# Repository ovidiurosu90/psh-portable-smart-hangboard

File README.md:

# [PSH Portable Smart Hangboard](https://github.com/ovidiurosu90/psh-portable-smart-hangboard)

## Abstract
### Problem
Help people get better at climbing by improving their finger strength

### Solution
Provide a portable smart hangboard to use for finger strength training

### How
- the whole project is open-source, and can be replicated by interested parties (note it requires a variety of skills like setting up a web server, 3d printing, soldering & crimping)
- the hangboard measures the pressure applied to the hanghold by using a couple of load cells
- the training plans are set in Google Sheets

## Important Links

| Name | README |
| --------------------- | ------------- |
| BOM Bill Of Materials | [BOM.md](BOM.md) |
| How To Build | [HOWTOBUILD.md](HOWTOBUILD.md) |

## Images

## Functionality of switches
- There are 3 big black momentary switches (labeled SW1, SW2 and SW3)
- There are 3 small toggle switches (labeled SW4, SW5 and SW6)
- The functionality of the switches is described below

### SW1
If SW4 is toggled ON: start training

Else: decrease volume

### SW2
If SW4 is toggled ON: start calibrating

Else: store volume into NVS (only if SW5 is toggled ON)

### SW3
If SW4 is toggled ON: end training

Else: increase volume

### SW4
If toggled ON: show train menu

Else: show volume menu

### SW5
If toggled ON: allow NVS to be updated (for calibration and for volume)

Else: don't allow NVS to be updated

### SW6
Not used at the moment

## Usage
- Power the microcontroller via its micro-USB port (+5V)
- Wait for the microcontroller to finish setting things up (it's ready when it says 'idle' on the lower left side of analog meter)
- Configure the training parameters in the spreadsheet via Goole Sheets
- The training program starts with a rest cycle, followed by an activity cycle, then repeat
- Example

| totalCycles | activityTotalSeconds | restTotalSeconds | scaleLowerLimitGrams | scaleUpperLimitGrams |
| ----------- | -------------------- | ---------------- | -------------------- | -------------------- |
| 6           | 10                   | 20               | 55000                | 90000                |

- For the example above, we'll have 6 cycles as follows:
    - cycle 1: rest for 20 seconds
    - cycle 2: activity for 10 seconds
    - cycle 3: rest for 20 seconds
    - cycle 4: activity for 10 seconds
    - cycle 5: rest for 20 seconds
    - cycle 6: activity for 10 seconds

- Start the training by pressing SW1 (note SW4 should be toggled ON)
- The score is updated only in the activity cycles (cycle 2, 4 and 6 in the example above)
- The score is calculated as follows:
    - each second there are 2 scale measurements
    - let's say we have 3 activity cycles of 10 seconds
    - which means 3x 10x 2 measurements
    - we just sum up the 60 measurements (in kg)
- For the exapmle above, the score can be the following:
    - score: 2017 (which is a sum of all the scale measurements)
    - history: 73,70,70,68,71,70,70,70,69,70,62,65,67,68,66,66,66,67,64,64,68,66,67,67,67,65,66,67,65,63
- In the future, the scoring method may be different, as at the moment, we don't penalize out-of-bounds measurements, and we don't reward in-bounds measurements

## Wiring

| [NodeMcu ESP-32S Lua ESP-WROOM-32](https://opencircuit.shop/product/nodemcu-esp-32s-lua-esp-wroom-32-wifi) | [SparkFun HX711 Load Cell Amplifier](https://eu.robotshop.com/products/hx711-load-cell-amplifier?variant=42600661942440) => NOTE we need to solder male pins |
| ---------------------------------------------------------------------------------------------------------- | ------------------------------------------------------------------------------------------------------------------------------------------------------------ |
| 5, 4                                                                                                       | DAT1, CLK1                                                                                                                                                   |
| 16, 15                                                                                                     | DAT2, CLK2                                                                                                                                                   |
| +3.3V                                                                                                      | VDD, VCC                                                                                                                                                     |
| GND                                                                                                        | GND                                                                                                                                                          |

| [NodeMcu ESP-32S Lua ESP-WROOM-32](https://opencircuit.shop/product/nodemcu-esp-32s-lua-esp-wroom-32-wifi) | [AZDelivery ST7735 SPI TFT Display 1.8 inch 128 x 160 pixels](https://www.amazon.nl/dp/B078J5TS2G/ref=pe_28126711_487805961_TE_item?th=1) =>  [guide](https://www.az-delivery.de/en/blogs/azdelivery-blog-fur-arduino-und-raspberry-pi/1-8-toll-tft-am-esp-32-dev-kit-c-betreiben) |
| ---------------------------------------------------------------------------------------------------------- | ---------------------------------------------------------------------------------------------------------------------------------------------------------------------------------------------------------------------------------------------------------------------------------- |
| +5V                                                                                                        | VCC                                                                                                                                                                                                                                                                                |
| GND                                                                                                        | GND                                                                                                                                                                                                                                                                                |
| G17                                                                                                        | CS                                                                                                                                                                                                                                                                                 |
| G14                                                                                                        | Reset / RST                                                                                                                                                                                                                                                                        |
| G2                                                                                                         | A0 / DC                                                                                                                                                                                                                                                                            |
| G23                                                                                                        | Sda / MOSI                                                                                                                                                                                                                                                                         |
| G18                                                                                                        | Sck / SCLK                                                                                                                                                                                                                                                                         |
| 3.3V                                                                                                       | LED                                                                                                                                                                                                                                                                                |

| [NodeMcu ESP-32S Lua ESP-WROOM-32](https://opencircuit.shop/product/nodemcu-esp-32s-lua-esp-wroom-32-wifi) | [AZDelivery ST7735 SPI TFT Display 1.8 inch 128 x 160 pixels](https://www.amazon.nl/dp/B078J5TS2G/ref=pe_28126711_487805961_TE_item?th=1) => [guide](https://randomnerdtutorials.com/guide-to-1-8-tft-display-with-arduino/) |
| ---------------------------------------------------------------------------------------------------------- | ---------------------------------------------------------------------------------------------------------------------------------------------------------------------------------------------------------------------------- |
| G33                                                                                                        | CS                                                                                                                                                                                                                           |
| G23                                                                                                        | MOSI (shared with display)                                                                                                                                                                                                   |
| G19                                                                                                        | MISO                                                                                                                                                                                                                         |
| G18                                                                                                        | SCK / SCLK (shared with display                                                                                                                                                                                              |

NOTE At the moment the custom PCB for the MainControllerNodeMCU-32S module needs a small improvement. Currently it’s missing a 4-pin connection for interfacing with the SD card on the TFT display. You can either modify the project and add the connector on the PCB (before placing the order), or make the 4 connections manually (solder the 4 wires directly on the PCB, picture found below). Follow the issue on GitHub for updates: [\[PCB\] Update Custom PCB for MainControllerNodeMCU-32S #8](https://github.com/ovidiurosu90/psh-portable-smart-hangboard/issues/8).

| [NodeMcu ESP-32S Lua ESP-WROOM-32](https://opencircuit.shop/product/nodemcu-esp-32s-lua-esp-wroom-32-wifi) | [SparkFun MAX98357A I2S Audio Breakout](https://opencircuit.shop/product/sparkfun-i2s-audio-breakout-max98357a) => [guide](https://learn.sparkfun.com/tutorials/i2s-audio-breakout-hookup-guide/all) |
| ---------------------------------------------------------------------------------------------------------- | ---------------------------------------------------------------------------------------------------------------------------------------------------------------------------------------------------- |
| +5V (if we use +3.3V the volume fluctuates)                                                                | VDD                                                                                                                                                                                                  |
| GND                                                                                                        | GND                                                                                                                                                                                                  |
| \-                                                                                                         | SD                                                                                                                                                                                                   |
| GND                                                                                                        | GAIN (+12dB, without this it will be +9dB)                                                                                                                                                           |
| G22                                                                                                        | DIN / DOUT                                                                                                                                                                                           |
| G26                                                                                                        | BCLK                                                                                                                                                                                                 |
| G25                                                                                                        | LRCLK                                                                                                                                                                                                |

| [NodeMcu ESP-32S Lua ESP-WROOM-32](https://opencircuit.shop/product/nodemcu-esp-32s-lua-esp-wroom-32-wifi) | SwitchesModule (my custom PCB) |
| ---------------------------------------------------------------------------------------------------------- | ------------------------------ |
| G21                                                                                                        | SW1                            |
| G27                                                                                                        | SW2                            |
| G13                                                                                                        | SW3                            |
| GND                                                                                                        | GND                            |
| +3.3V                                                                                                      | ~ pull-up resistors            |
| G36                                                                                                        | SW4 with 10k resistor to +3.3V |
| G39                                                                                                        | SW5 with 10k resistor to +3.3V |
| G35                                                                                                        | SW6 with 10k resistor to +3.3V |
| GND                                                                                                        | GND                            |

| [NodeMcu ESP-32S Lua ESP-WROOM-32](https://opencircuit.shop/product/nodemcu-esp-32s-lua-esp-wroom-32-wifi) | ?         |
| ---------------------------------------------------------------------------------------------------------- | --------- |
| G32 (input-output pin)                                                                                     | Available |
| G34 (only output pin)                                                                                      | Available |

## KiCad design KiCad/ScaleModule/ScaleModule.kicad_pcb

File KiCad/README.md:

# KiCad
I am using KiCad 8.0 as the main electronics design software. The project at the moment has 3 custom PCBs that were designed with this tool.
You have to send the gerber files to a PCB manufacturer, then solder the connectors / components before assembling.

## Images

## Configuration
### PCB Layers
- F.Cu => tracks & maybe name + version
- B.Cu => tracks & maybe name + version
- F.Adhesive => vias + pads
- B.Adhesive => vias + pads
- F.Paste => vias + pads
- B.Paste => vias + pads
- F.Silkscreen => labels front
- B.Silkscreen => labels back + pcb dimensions (NOTE in 3D Viewer, you have to make visible Off-board Silkscreen)
- F.Mask => pads
- B.Mask => pads
- User.Comments => mounting holes exterior
- Edge.Cuts => pcb edges
- F.Courtyard => edges components on the pcb front
- B.Courtyard => edges components on the pcb back
- F.Fab => references footprints front
- B.Fab => references footprints back

### Design Rules -> Constraints
- Minimum track width 0.2 mm
- Minimum via diameter => 0.7 mm
- Minimum through hole => 0.4 mm
- Hole to hole clearance => 0.25mm
- Minimum uVia diameter => 0.7 mm
- Minimum uVia hole => 0.4mm
- Minimum text height => 0.5mm

### Design Rules -> Net Classes
- Default
    - Clearance 0.2 mm
    - Track Width 0.2 mm
    - Via Size 0.6 mm
    - Via Hole 0.3 mm
    - uVia Size 0.3 mm
    - uVia Hole 0.1 mm
    - DP Width 0.2
    - DP Gap 0.25 mm
- Custom
    - Clearance 0.3 mm
    - Track Width 0.3 mm
    - Via Size 0.8 mm
    - Via Hole 0.4 mm
    - uVia Size 0.6 mm
    - uVia Hole 0.2 mm
    - DP Width 0.2
    - DP Gap 0.25 mm
- Power
    - Clearance 0.8 mm
    - Track Width 0.8 mm
    - Via Size 1.2 mm
    - Via Hole 0.6 mm
    - uVia Size 0.6 mm
    - uVia Hole 0.2 mm
    - DP Width 0.2
    - DP Gap 0.25 mm

### Design Rules -> Pre-defined Sizes
- Tracks 1 mm width
- Vias 1.2 mm diameter, 1 mm hole
*Tracks: 1 mm for power, netclass width for everything else*

## Validation
A. Schematic Editor
1. Annotate Schematic => make screenshots
2. Electrical Rules Checker
3. Assign Footprints => make screenshots

B. PCB Editor
0. File -> Board Setup -> Import Settings from Another Board...
1. Check F.Cu with unfill zones => make screenshots
2. Check B.Cu with unfill zones => make screenshots
3. Check F.Cu with fill zones => make screenshots
4. Check B.Cu with fill zones => make screenshots
5. Check 3D Viewer front (toggle Through-hole Models on & off) => make screenshots
6. Check 3D Viewer back (toggle Through-hole Models on & off) => make screenshots

7. Check the connections
8. Check order & orientation of the pins for the connectors (e.g. JST-XH)
9. Check pcb size
10. Check version on both F.Cu / B.Cu & page print

11. Update PCB From Schematic (uncheck Delete footprints with no symbols)
12. Design Rules Checker

## Generate Gerber & Drill files
Check [wiki from JLCPCB](https://jlcpcb.com/help/article/362-how-to-generate-gerber-and-drill-files-in-kicad-7)

1. In PCB Editor => File => Fabrication Outputs => Gerbers
2. Select Output directory: Outputs
3. Include Layers
    * F.Cu
    * B.Cu
    * F.Paste
    * B.Paste
    * F.Silkscreen
    * B.Silkscreen
    * F.Mask
    * B.Mask
    * Edge.Cuts
4. Check Plot reference designators
5. Check Check zone files before plotting
6. Check Use Protel filename extensions
7. Check Subtract soldermask from silkscreen

8. Click Plot

9. Click Generate Drill Files
10. Check Use alternate drill mode
11. Check Absolute for Drill Origin
12. Check Milimeters for Drill Units
13. Check Decimal format for Zeros Format

14. Click Generate Drill File
15. Click Generate Map File

## Verify generated Gerber files
* Open Gerber Viewer in KiCad
* File -> Open Excellon Drill File (do it once for each drill file you have)
* File -> Open Gerber Plot File => Edge_Cuts
* File -> Open Gerber Plot File => F_Silkscreen
* File -> Open Gerber Plot File => F_Mask
* File -> Open Gerber Plot File => F_Cu
* File -> Open Gerber Plot File => B_Silkscreen
* File -> Open Gerber Plot File => B_Mask
* File -> Open Gerber Plot File => B_Cu

* Create a zip file from all the files in the Outputs directory & add the version & date to the name (e.g. *MainControllerNodeMCU-32S-v0.1-20240428.zip*)

## Add the zip to your PCB manufacturer (e.g.)
* Go to https://cart.jlcpcb.com/quote
* Check dimensions (auto-generated)
* Check version (on the PCB)
* Select black or white (if it's not too expensive or slow)
* Check mounting holes

* IMPORTANT Check if you want to create or update another board, to save on transport

# Task List
## MainControllerNodeMCU-32S v0.1-20240428
- NOTE At the moment the custom PCB for the MainControllerNodeMCU-32S module needs a small improvement. Currently it’s missing a 4-pin connection for interfacing with the SD card on the TFT display. You can either modify the project and add the connector on the PCB (before placing the order), or make the 4 connections manually (solder the 4 wires directly on the PCB, picture found below). Follow the issue on GitHub for updates: [\[PCB\] Update Custom PCB for MainControllerNodeMCU-32S #8](https://github.com/ovidiurosu90/psh-portable-smart-hangboard/issues/8)

## ScaleModule v0.1-20240428
- All done

## SwitchesModule v0.1-20240428
- All done

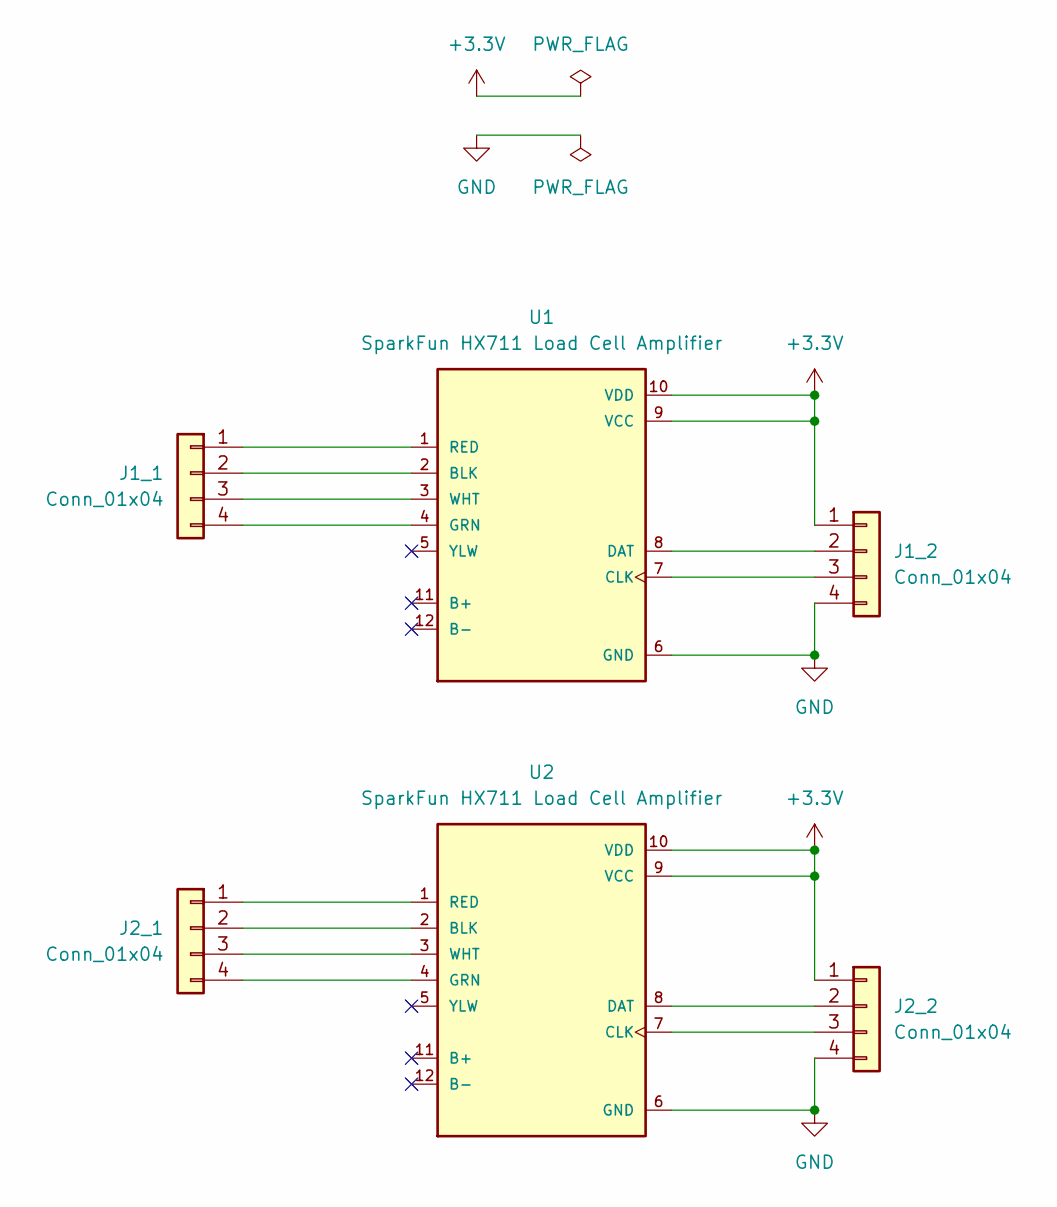
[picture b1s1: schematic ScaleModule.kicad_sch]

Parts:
J1_1, J1_2, J2_1, J2_2: Conn_01x04; JST_XH_B4B-XH-A_1x04_P2.50mm_Vertical
U1, U2: SparkFun HX711 Load Cell Amplifier

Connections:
+3.3V: J1_2.1, J2_2.1, U1.9 (VCC), U1.10 (VDD), U2.9 (VCC), U2.10 (VDD)
GND: J1_2.4, J2_2.4, U1.6 (GND), U2.6 (GND)
unnamed: J1_1.1, U1.1 (RED)
unnamed: J1_1.2, U1.2 (BLK)
unnamed: J1_1.3, U1.3 (WHT)
unnamed: J1_1.4, U1.4 (GRN)
unnamed: J1_2.2, U1.8 (DAT)
unnamed: J1_2.3, U1.7 (CLK)
unnamed: J2_1.1, U2.1 (RED)
unnamed: J2_1.2, U2.2 (BLK)
unnamed: J2_1.3, U2.3 (WHT)
unnamed: J2_1.4, U2.4 (GRN)
unnamed: J2_2.2, U2.8 (DAT)
unnamed: J2_2.3, U2.7 (CLK)

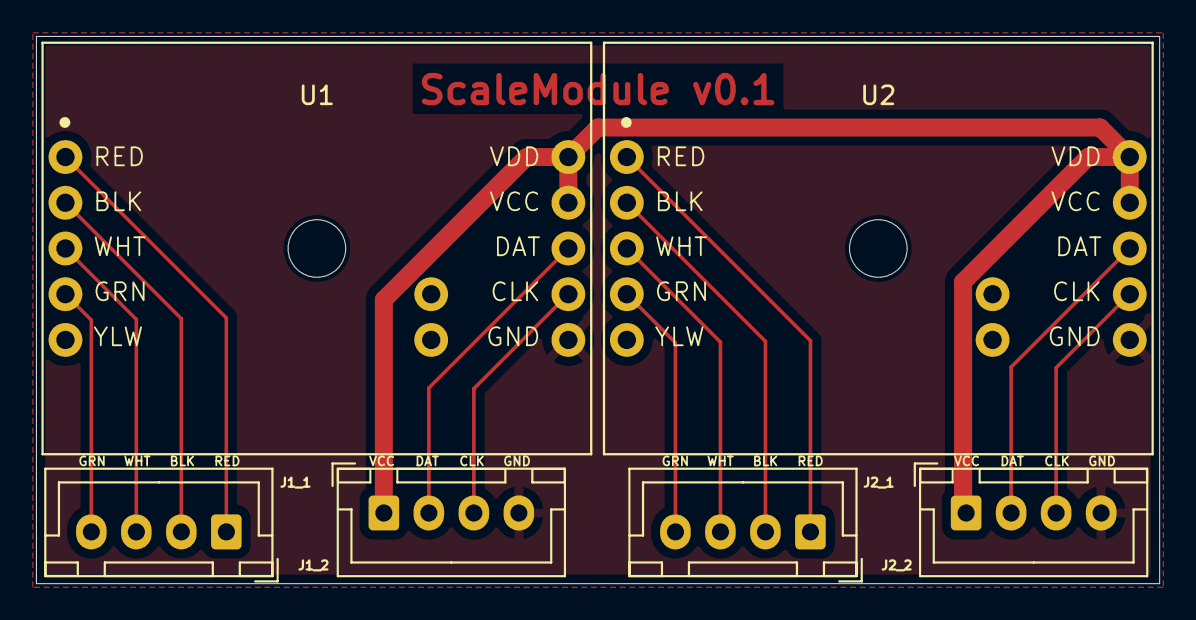
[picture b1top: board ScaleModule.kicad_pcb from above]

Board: 2 copper layers, 62.4 x 30.4 mm, 8 parts (0 on the bottom side), 14 nets.

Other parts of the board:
MountingHole1, MountingHole2: MountingHole_3.2mm_M3

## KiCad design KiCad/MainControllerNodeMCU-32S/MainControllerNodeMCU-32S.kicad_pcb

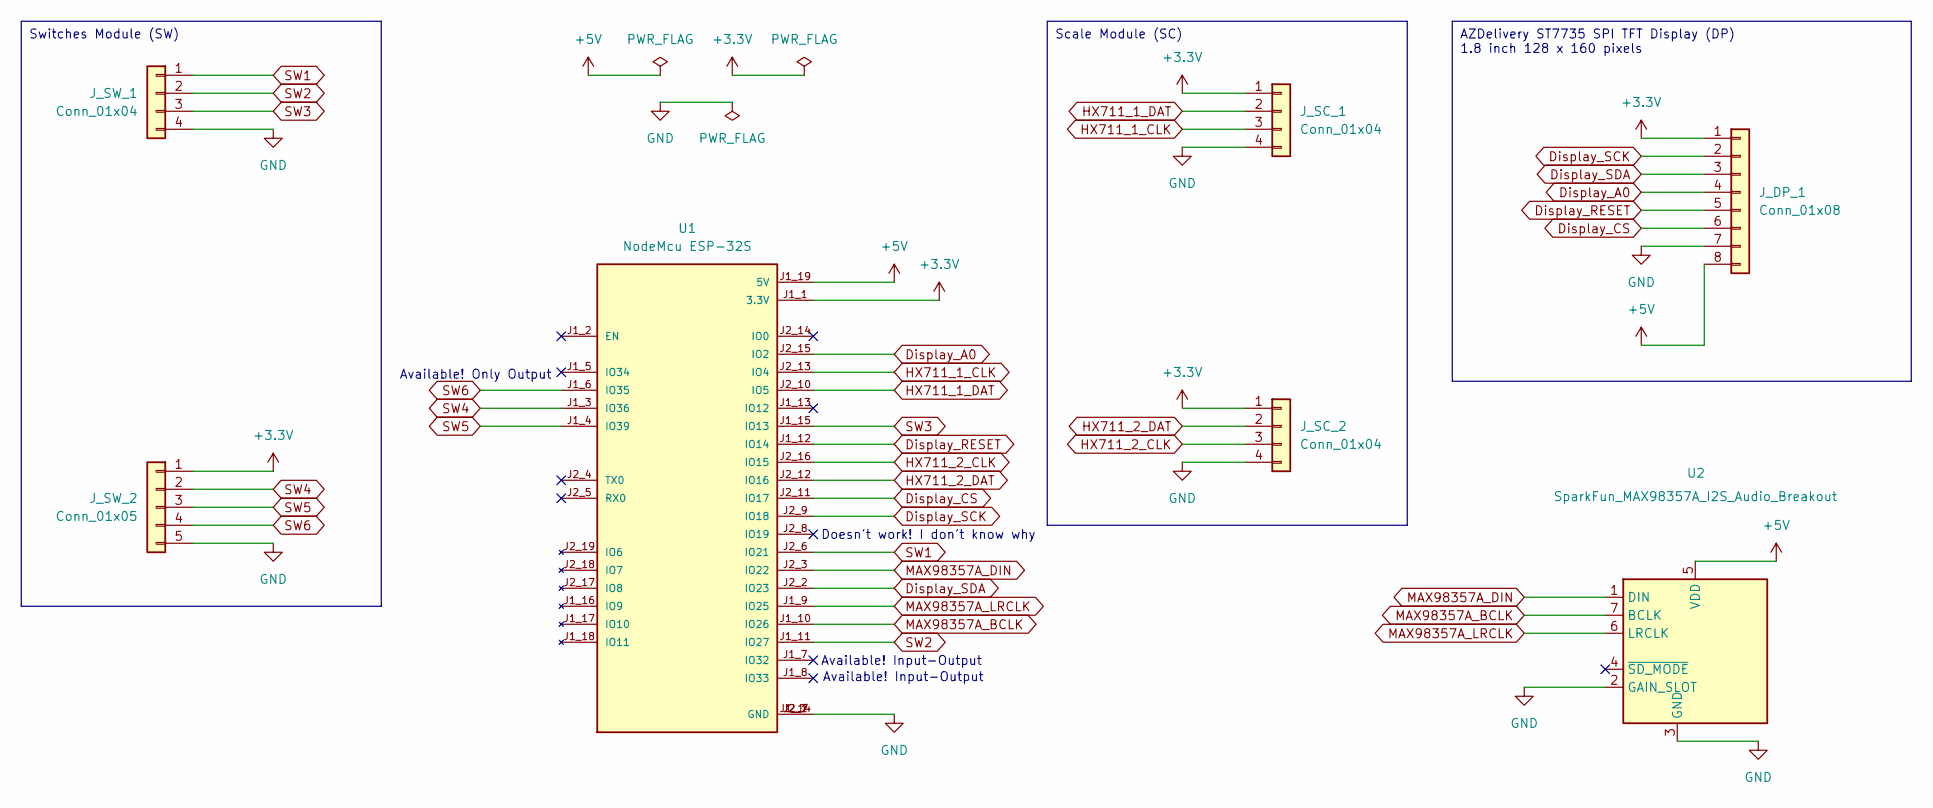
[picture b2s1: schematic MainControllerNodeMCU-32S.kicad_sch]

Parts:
J_DP_1: Conn_01x08; PinHeader_1x08_P2.54mm_Vertical
J_SC_1, J_SC_2: Conn_01x04; JST_XH_B4B-XH-A_1x04_P2.50mm_Vertical
J_SW_1: Conn_01x04; JST_XH_B4B-XH-A_1x04_P2.50mm_Vertical
J_SW_2: Conn_01x05; JST_XH_B5B-XH-A_1x05_P2.50mm_Vertical
U1: NodeMcu ESP-32S; PARTREV V1
U2: SparkFun_MAX98357A_I2S_Audio_Breakout; SparkFun MAX98357A I2S Audio Breakout

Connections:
+3.3V: J_DP_1.1, J_SC_1.1, J_SC_2.1, J_SW_2.1, U1.J1_1 (3.3V)
+5V: J_DP_1.8, U1.J1_19 (5V), U2.5 (VDD)
Display_A0: J_DP_1.4, U1.J2_15 (IO2)
Display_CS: J_DP_1.6, U1.J2_11 (IO17)
Display_RESET: J_DP_1.5, U1.J1_12 (IO14)
Display_SCK: J_DP_1.2, U1.J2_9 (IO18)
Display_SDA: J_DP_1.3, U1.J2_2 (IO23)
GND: J_DP_1.7, J_SC_1.4, J_SC_2.4, J_SW_1.4, J_SW_2.5, U1.J1_14 (GND), U1.J2_1 (GND), U1.J2_7 (GND), U2.2 (GAIN_SLOT), U2.3 (GND)
HX711_1_CLK: J_SC_1.3, U1.J2_13 (IO4)
HX711_1_DAT: J_SC_1.2, U1.J2_10 (IO5)
HX711_2_CLK: J_SC_2.3, U1.J2_16 (IO15)
HX711_2_DAT: J_SC_2.2, U1.J2_12 (IO16)
MAX98357A_BCLK: U1.J1_10 (IO26), U2.7 (BCLK)
MAX98357A_DIN: U1.J2_3 (IO22), U2.1 (DIN)
MAX98357A_LRCLK: U1.J1_9 (IO25), U2.6 (LRCLK)
SW1: J_SW_1.1, U1.J2_6 (IO21)
SW2: J_SW_1.2, U1.J1_11 (IO27)
SW3: J_SW_1.3, U1.J1_15 (IO13)
SW4: J_SW_2.2, U1.J1_3 (IO36)
SW5: J_SW_2.3, U1.J1_4 (IO39)
SW6: J_SW_2.4, U1.J1_6 (IO35)

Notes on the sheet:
Switches Module (SW)
Scale Module (SC)
AZDelivery ST7735 SPI TFT Display (DP) 1.8 inch 128 x 160 pixels
Available! Only Output
Available! Input-Output
Doesn't work! I don't know why

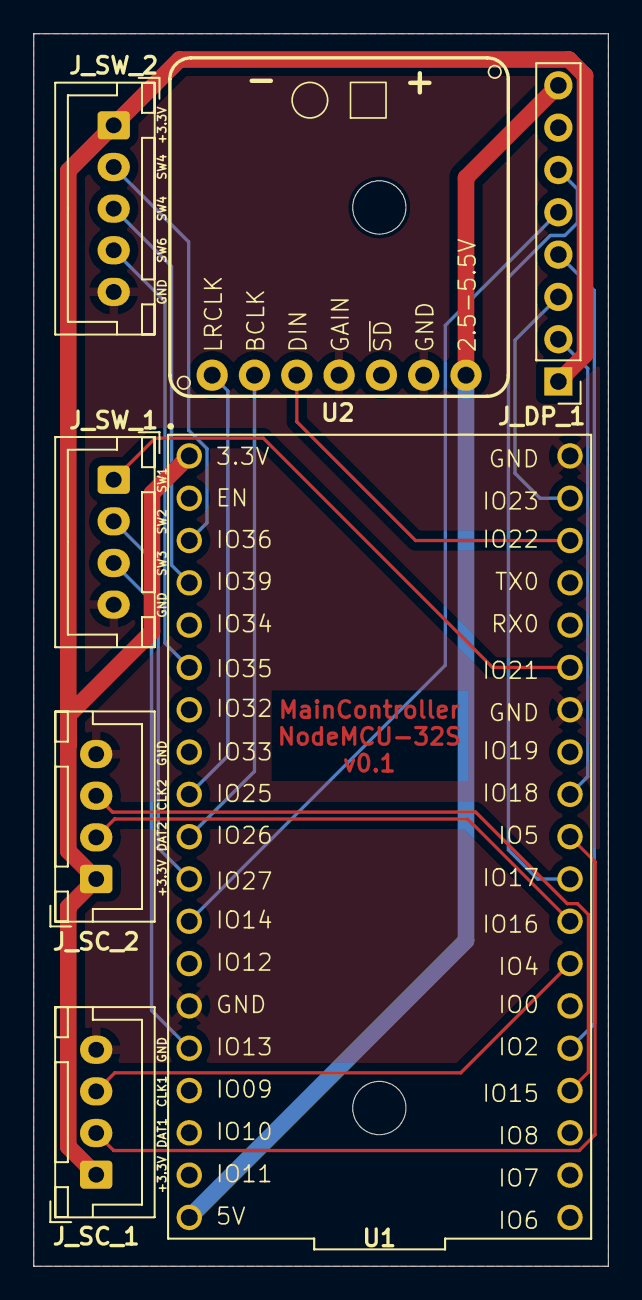
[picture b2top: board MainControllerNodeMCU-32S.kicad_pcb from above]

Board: 2 copper layers, 34.5 x 74.0 mm, 9 parts (0 on the bottom side), 21 nets.

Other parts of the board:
MountinHole2: MountingHole_3.2mm_M3
MountingHole1: MountingHole_3.2mm_M3

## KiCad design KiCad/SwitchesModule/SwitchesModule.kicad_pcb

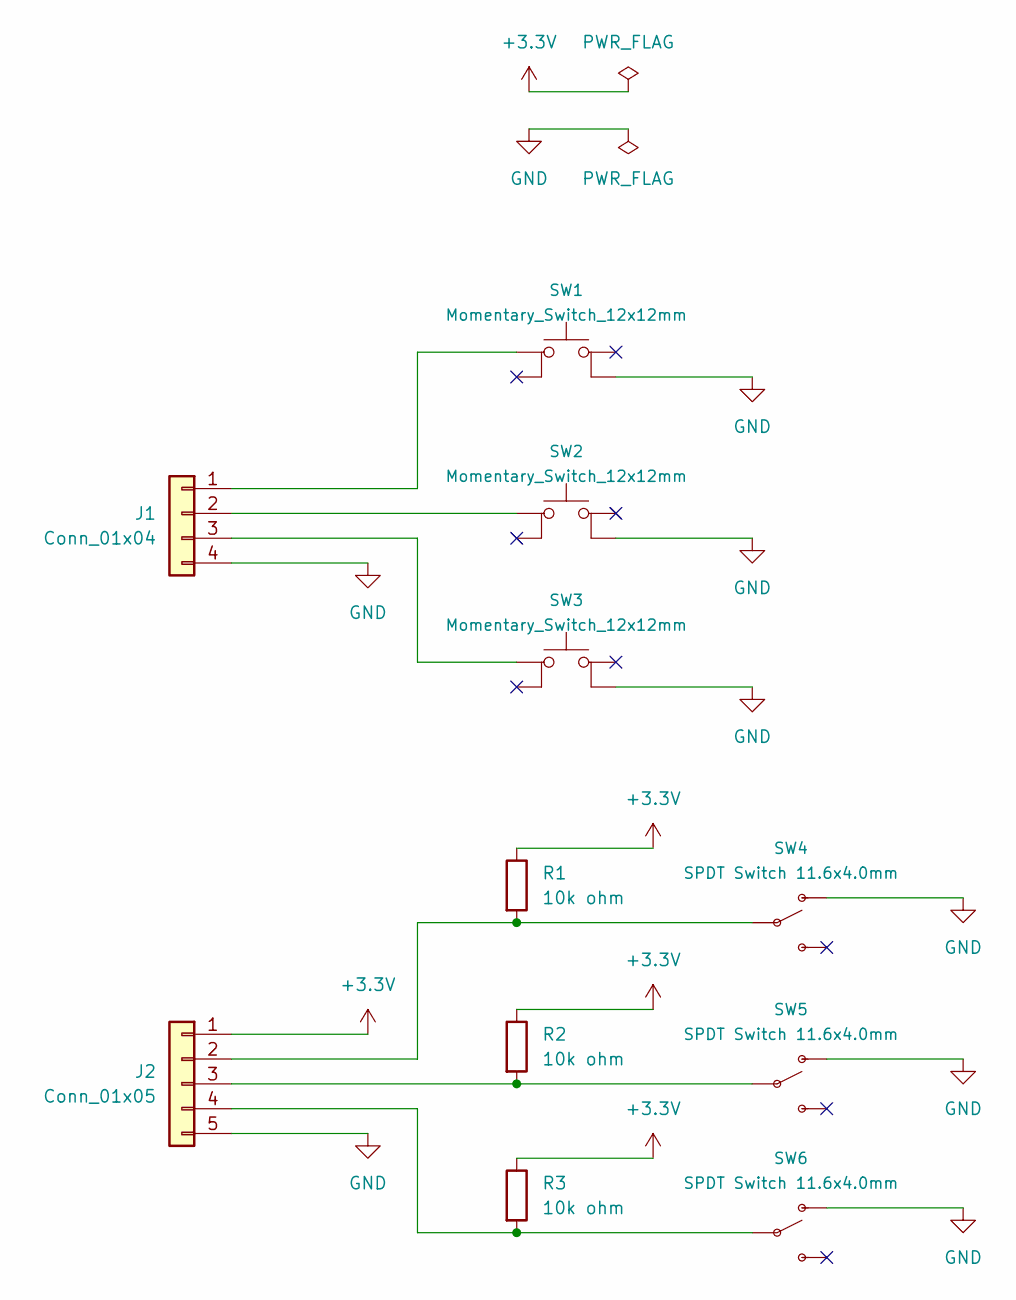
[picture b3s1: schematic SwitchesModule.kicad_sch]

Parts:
J1: Conn_01x04; JST_XH_B4B-XH-A_1x04_P2.50mm_Vertical
J2: Conn_01x05; JST_XH_B5B-XH-A_1x05_P2.50mm_Vertical
R1, R2, R3: 10k ohm; R_Axial_DIN0207_L6.3mm_D2.5mm_P7.62mm_Horizontal
SW1, SW2, SW3: Momentary_Switch_12x12mm; Momentary Switch 12x12mm
SW4, SW5, SW6: SPDT Switch 11.6x4.0mm

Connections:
+3.3V: J2.1, R1.1, R2.1, R3.1
GND: J1.4, J2.5, SW1.3 (K), SW2.3 (K), SW3.3 (K), SW4.1 (O), SW5.1 (O), SW6.1 (O)
unnamed: J1.1, SW1.1
unnamed: J1.2, SW2.1
unnamed: J1.3, SW3.1
unnamed: J2.2, R1.2, SW4.2
unnamed: J2.3, R2.2, SW5.2
unnamed: J2.4, R3.2, SW6.2

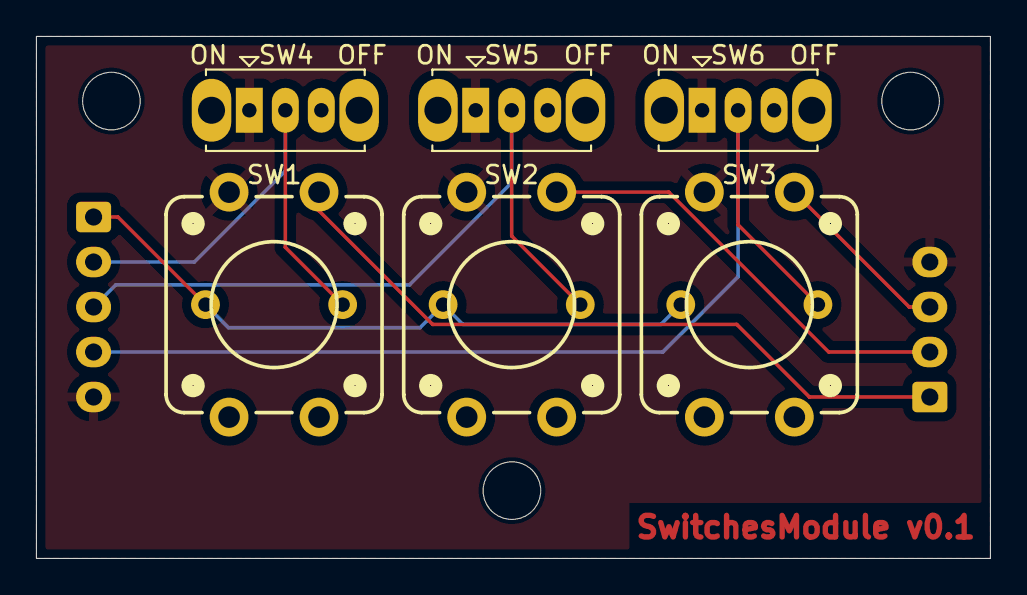
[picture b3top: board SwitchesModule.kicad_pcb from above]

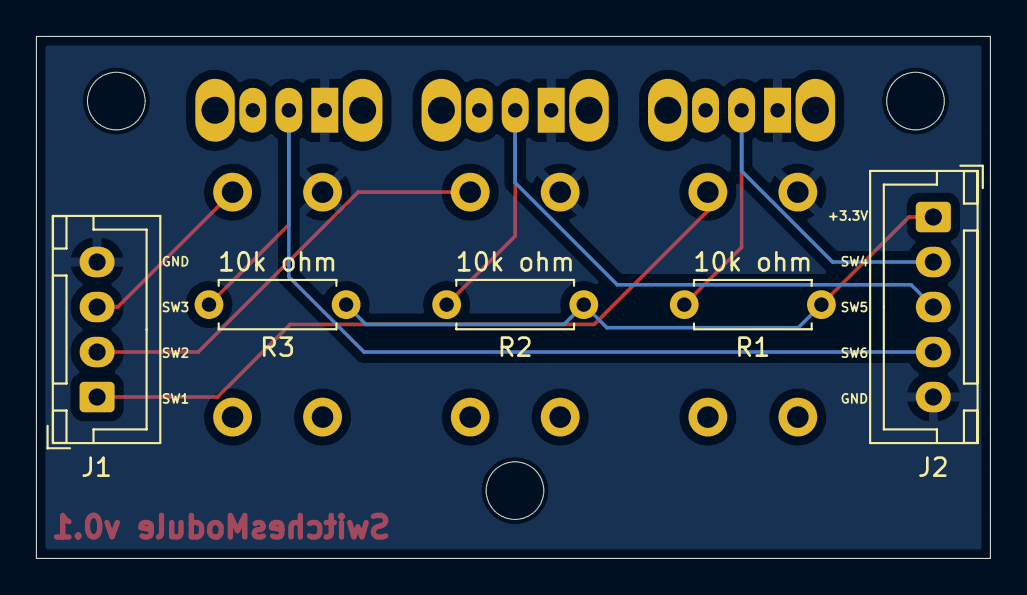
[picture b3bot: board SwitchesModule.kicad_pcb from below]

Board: 2 copper layers, 53.0 x 29.0 mm, 14 parts (5 on the bottom side), 8 nets.

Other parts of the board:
MountingHole1, MountingHole2, MountingHole3: MountingHole_3.2mm_M3

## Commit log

2024-05-12 [all] Initial commit
2024-05-13 [Arduino] Display cycle stats on the screen
2024-05-13 [Arduino] Compute score and display it on the screen
2024-05-13 [Images|KiCad] Adding Images in the root directory + adding documentation & images for KiCad
2024-05-14 [Web|Arduino #3] Send score to Google Sheets via WiFi
2024-05-14 [Arduino #1] Configure toggle switches
2024-05-14 [all|KiCad #6] Add notes in the relevant places that the custom PCB for the MainControllerNodeMCU-32S is missing the connector for the SD card
2024-05-14 [all #5] Add BOM Bill of Materials to GitHub
2024-05-14 [Arduino #2] Update scale thresholds on the display from the configuration
2024-05-16 [Arduino|Web #9] Fetch training configuration before each training
2024-05-16 [Arduino #4] Profile boot time - it takes 10s for the switches to be responsive
2024-05-20 [all #11] Document how scoring works and improve usage documentation
2024-05-23 [all #7] [DOC] Create step by step guide with links and pictures on how to build this
2024-09-20 [CAD] Adding Wood non-slippery holds
